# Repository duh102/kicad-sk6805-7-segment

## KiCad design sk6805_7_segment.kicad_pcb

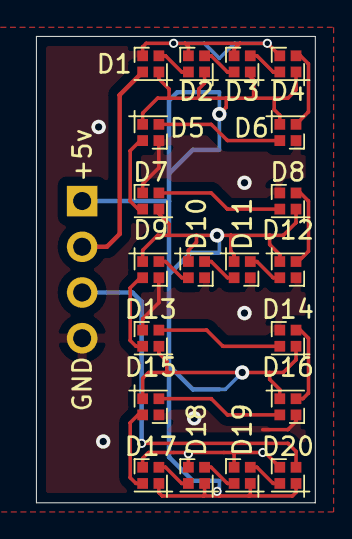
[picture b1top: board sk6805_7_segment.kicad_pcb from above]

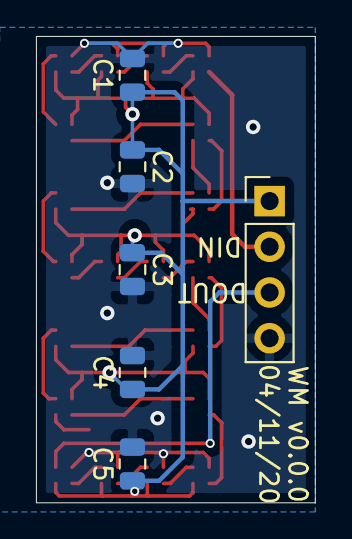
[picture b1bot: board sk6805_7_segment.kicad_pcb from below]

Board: 2 copper layers, 15.5 x 25.9 mm, 26 parts (6 on the bottom side), 23 nets.

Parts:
C1, C2, C3, C4, C5: 0.1uF; C_0805_2012Metric
D1, D2, D3, D4, D5, D6, D7, D8, D9, D10, D11, D12, D13, D14, D15, D16, D17, D18, D19, D20: SK6805_1515; LED_SK6805_PLCC4_1.5x1.5mm_P0.65mm
J1: PinHeader_1x04_P2.54mm_Vertical

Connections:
+5V: C1.1, C2.1, C3.1, C4.1, C5.1, D1.4, D2.4, D3.4, D4.4, D5.4, D6.4, D7.4, D8.4, D9.4, D10.4, D11.4, D12.4, D13.4, D14.4, D15.4, D16.4, D17.4, D18.4, D19.4, D20.4, J1.1
/DIN: D1.3, J1.2
/DOUT: D20.1, J1.3
GND: C1.2, C2.2, C3.2, C4.2, C5.2, D1.2, D2.2, D3.2, D4.2, D5.2, D6.2, D7.2, D8.2, D9.2, D10.2, D11.2, D12.2, D13.2, D14.2, D15.2, D16.2, D17.2, D18.2, D19.2, D20.2, J1.4
unnamed: D1.1, D2.3
unnamed: D2.1, D3.3
unnamed: D3.1, D4.3
unnamed: D4.1, D6.3
unnamed: D5.1, D7.3
unnamed: D5.3, D6.1
unnamed: D7.1, D8.3
unnamed: D9.3, D10.1
unnamed: D10.3, D11.1
unnamed: D11.3, D12.1
unnamed: D8.1, D12.3
unnamed: D13.1, D14.3
unnamed: D9.1, D13.3
unnamed: D14.1, D16.3
unnamed: D15.1, D17.3
unnamed: D15.3, D16.1
unnamed: D17.1, D18.3
unnamed: D18.1, D19.3
unnamed: D19.1, D20.3

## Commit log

2020-04-12 Add gbr output folder
2020-12-09 Update gitignore
